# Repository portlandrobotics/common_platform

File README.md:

<!-- PROJECT SHIELDS -->
<!--
*** I'm using markdown "reference style" links for readability.
*** Reference links are enclosed in brackets [ ] instead of parentheses ( ).
*** See the bottom of this document for the declaration of the reference variables
*** for contributors-url, forks-url, etc. This is an optional, concise syntax you may use.
*** https://www.markdownguide.org/basic-syntax/#reference-style-links
-->
[![Contributors][contributors-shield]][contributors-url]
[![Forks][forks-shield]][forks-url]
[![Stargazers][stars-shield]][stars-url]
[![Issues][issues-shield]][issues-url]
[![MIT License][license-shield]][license-url]

<!-- PROJECT LOGO -->
<br />
<div align="center">

  <h3 align="center">Portland Area Robotics Society -- Common Robotics Platform</h3>

  <p align="center">
    Build and master the Common Robotics Platform with Portland Area Robotics Society 
    <br />
    <a href="https://parts-common-platform.readthedocs.io/en/latest/"><strong>Explore the docs »</strong></a>
    <br />
    <br />
    <a href="https://github.com/portlandrobotics/common_platform">View Demo</a>  <!-- TODO We need to add a demo video here -->
    ·
    <a href="https://github.com/portlandrobotics/common_platform/issues">Report Bug</a>
    ·
    <a href="https://github.com/portlandrobotics/common_platform/issues">Request Feature</a>
  </p>
</div>

<!-- TABLE OF CONTENTS -->
<details>
  <summary>Table of Contents</summary>
  <ol>
    <li>
      <a href="#about-the-project">About The Project</a>
      <ul>
        <li><a href="#built-with">Built With</a></li>
      </ul>
    </li>
    <li>
      <a href="#getting-started">Getting Started</a>
      <ul>
        <li><a href="#prerequisites">Prerequisites</a></li>
        <li><a href="#installation">Installation</a></li>
      </ul>
    </li>
    <li><a href="#usage">Usage</a></li>
    <li><a href="#roadmap">Roadmap</a></li>
    <li><a href="#contributing">Contributing</a></li>
    <li><a href="#license">License</a></li>
    <li><a href="#contact">Contact</a></li>
    <li><a href="#acknowledgments">Acknowledgments</a></li>
  </ol>
</details>

<!-- ABOUT THE PROJECT -->
## About The Project

<br>
<p align="center">
  
</p>
<br>

Our project centers around the innovative construction and programming of a versatile robot using the robust Pololu Romi Chassis Kit as its foundation. At the heart of our design is a custom carrier PCB, which integrates seamlessly with the chassis, ensuring a compact and efficient layout. 

<br>
<p align="center">
  
<br>
<br>

Key components of our build include two TB9051FTG Single Brushed DC Motor Driver Carriers for precise motion control, and a Pololu 5V, 2.5A Step-Down Voltage Regulator D24V22F5 to ensure stable power supply. Navigation and orientation are handled by the sophisticated MPU-9250 9DOF Module, a nine-axis sensor that offers unparalleled accuracy in movement tracking. Additional hardware includes a set of Romi Encoders, a Romi Chassis Caster for stable maneuverability, and a powerful Teensy 4.0 microcontroller for robust processing capabilities. We've also incorporated an SPDT slide switch and two IRFU5505PBF transistors, supported by a suite of nine resistors of varying values to fine-tune our circuitry. 

<br>
<p align="center">
  
</p>
<br>

Looking towards the future, our vision is to enhance this platform by integrating a Raspberry Pi, aiming to achieve autonomous functionality through the advanced capabilities of ROS2. This robot is not just a machine, but a gateway to exploring the vast possibilities of robotics, making it an ideal platform for enthusiasts and innovators alike in the Portland Area Robotics Society.

<p align="right">(<a href="#readme-top">back to top</a>)</p>

### Built With

* [![CPP][cpp]][cpp-url]
* [![C][c]][c-url]
* [![Python 3][python]][python-url]
* [![PlatformIO][platformio]][platformio-url]
* [![Arduino][arduino-ide]][arduino-url]
* [![KiCadEDA][kicad]][kicad-url]
* [![ROS][ros]][ros-url]

<p align="right">(<a href="#readme-top">back to top</a>)</p>

<!-- GETTING STARTED -->
## Getting Started

### Prerequisites

* All the required parts from the BOM on hand. [BOM](/BOM.csv)
* Windows/Mac/Linux PC
* Soldering supplies

### Installation

Welcome to the setup guide for the PARTS Common Robotics Platform. Follow these steps to prepare your hardware and software for an exciting journey into robotics!

#### 1. Solder Your PARTS CRP Board
Soldering the PARTS CRP board is the first crucial step. Follow the instructions carefully to ensure a successful setup.

- **Interactive BOM**: Utilize the [Interactive BOM](https://htmlpreview.github.io/?https://github.com/portlandrobotics/common_platform/blob/master/hardware/romi_board/bom/ibom.html) for an easier soldering process.
- **Headers for Connectivity**: We recommend using headers for connections between boards. This makes disassembly possible if needed.
  - Use female (socket) headers on the bottom board.
  - Use male (pin) headers on the top board. These are typically included with all breakout boards.
- **MOSFET Orientation**: Ensure the correct orientation of the MOSFETs during soldering.
- **Resistor for Battery Voltage Divider**: Choose the resistor based on your battery choice:
  - Use a 2M ohm resistor (R1) for 6 AA batteries.
  - Opt for a 3M ohm resistor if using higher voltage batteries like 2 LiPo batteries.
  - Install a >100 pf capacitor across R2 to address voltage drop issues.
- **Teensy Board Modification**: For battery power, cut the trace on the Teensy board. Refer to the note "Cut to separate VIN from VUSB" on the [Teensy 4.0 Back Side](https://github.com/portlandrobotics/common_platform/blob/master/hardware/main_schematic.pdf) image.
- **Resistor Values**: The values of R4, R5, R8, R9 depend on your specific usage. For I2C, 4.7k is appropriate.
- **Schematic**: Refer to the [Main Schematic](https://github.com/portlandrobotics/common_platform/blob/master/hardware/main_schematic.pdf) for detailed understanding.

#### 2. Solder Accessories
Solder accessories like the Inertial Measurement Unit (IMU), ensuring proper orientation and connection.

#### 3. Assemble the Pololu Romi Chassis
The Pololu Romi Chassis forms the physical structure of your robot.

- Follow the [Romi Chassis Assembly Guide](https://www.pololu.com/docs/0J68/4) for detailed instructions on assembling the chassis.

#### 4. Install Arduino IDE
The Arduino Integrated Development Environment (IDE) is essential for programming your robot.

- Download and install the [Arduino IDE](https://www.arduino.cc/en/Main/Software) suitable for your operating system.

#### 5. Clone PARTS CRP Repository
Get the latest codebase for the PARTS CRP project by cloning the repository.

- Use Git to clone the repository or download it directly from the [PARTS CRP GitHub page](https://github.com/portlandrobotics/common_platform).

_For detailed instructions, please refer to the [Documentation](https://parts-common-platform.readthedocs.io/en/latest/)_

<p align="right">(<a href="#readme-top">back to top</a>)</p>

## Usage

This section provides practical examples of how to use the PARTS Common Robotics Platform effectively. We'll start with a basic test to ensure your setup is functioning correctly.

### Starting with the Basic Test

1. **Flash the Teensy 4.0 Board:**
   Begin by flashing the Teensy 4.0 board with the basic test code found in the repository at `/firmware/basic_test/basic_test.ino`. This initial test is crucial for validating your setup.

2. **Expected Behavior:**
   Upon successful flashing, the robot should exhibit a simple behavior pattern: moving forward, pausing, and then moving backward.

_For more examples, please refer to the [Documentation](https://parts-common-platform.readthedocs.io/en/latest/)_

<p align="right">(<a href="#readme-top">back to top</a>)</p>

<!-- ROADMAP -->
## Roadmap

- [ ] Build hardware library for common robotics platform
- [ ] Build manual for open robotics platform
     - [ ] SBC
     - [ ] Microcontroller
     - [ ] Software
     - [ ] Power
     - [ ] Motion
     - [ ] Communication
     - [ ] Sensors and cameras
     - [ ] Soldering
     - [ ] PCB design and ordering
- [ ] Create 3D model of platform for Gazebo and other sims
- [ ] ROS2 Setup
    - [ ] micro-ROS + ROS2 Humble
    - [ ] control
    - [ ] commuication
    - [ ] navigation
    - [ ] avoidance
 - [ ] Demo of system

See the [open issues](https://github.com/portlandrobotics/common_platform/issues) for a full list of proposed features (and known issues).

<p align="right">(<a href="#readme-top">back to top</a>)</p>

<!-- CONTRIBUTING -->
## Contributing

Contributions are what make the open source community such an amazing place to learn, inspire, and create. Any contributions you make are **greatly appreciated**.

If you have a suggestion that would make this better, please fork the repo and create a pull request. You can also simply open an issue with the tag "enhancement".
Don't forget to give the project a star! Thanks again!

1. Fork the Project
2. Create your Feature Branch (`git checkout -b feature/AmazingFeature`)
3. Commit your Changes (`git commit -m 'Add some AmazingFeature'`)
4. Push to the Branch (`git push origin feature/AmazingFeature`)
5. Open a Pull Request

<p align="right">(<a href="#readme-top">back to top</a>)</p>

<!-- LICENSE -->
## License

Distributed under the MIT License and the Solderpad Hardware License v2.1. See [LICENSE.txt][license-url] for more information.

<p align="right">(<a href="#readme-top">back to top</a>)</p>

<!-- MARKDOWN LINKS & IMAGES -->
<!-- https://www.markdownguide.org/basic-syntax/#reference-style-links -->
[contributors-shield]: https://img.shields.io/github/contributors/portlandrobotics/common_platform.svg?style=for-the-badge
[contributors-url]: https://github.com/portlandrobotics/common_platform/graphs/contributors
[forks-shield]: https://img.shields.io/github/forks/portlandrobotics/common_platform.svg?style=for-the-badge
[forks-url]: https://github.com/portlandrobotics/common_platform/network/members
[stars-shield]: https://img.shields.io/github/stars/portlandrobotics/common_platform.svg?style=for-the-badge
[stars-url]: https://github.com/portlandrobotics/common_platform/stargazers
[issues-shield]: https://img.shields.io/github/issues/portlandrobotics/common_platform.svg?style=for-the-badge
[issues-url]: https://github.com/portlandrobotics/common_platform/issues
[license-shield]: https://img.shields.io/badge/license-mit_%26_solderpad-brightgreen?style=for-the-badge
[license-url]: https://github.com/portlandrobotics/common_platform/blob/master/LICENSE.txt
[arduino-ide]: https://img.shields.io/badge/Arduino_IDE-00979D?style=for-the-badge&logo=arduino&logoColor=white
[arduino-url]: https://www.arduino.cc/en/software
[cpp]: https://img.shields.io/badge/C%2B%2B-00599C?style=for-the-badge&logo=c%2B%2B&logoColor=white
[cpp-url]: https://en.wikipedia.org/wiki/C%2B%2B
[c]: https://img.shields.io/badge/C-00599C?style=for-the-badge&logo=c&logoColor=white
[c-url]: https://en.wikipedia.org/wiki/C_(programming_language)
[python]: https://img.shields.io/badge/Python-3776AB?style=for-the-badge&logo=python&logoColor=white
[python-url]: https://www.python.org/
[platformio]: https://img.shields.io/badge/PlatformIO-F5822A.svg?style=for-the-badge&logo=PlatformIO&logoColor=white
[platformio-url]: https://platformio.org/
[kicad]: https://img.shields.io/badge/KiCad-314CB0.svg?style=for-the-badge&logo=KiCad&logoColor=white
[kicad-url]: https://www.kicad.org/
[ros]: https://img.shields.io/badge/ROS-22314E.svg?style=for-the-badge&logo=ROS&logoColor=white
[ros-url]:https://www.ros.org/

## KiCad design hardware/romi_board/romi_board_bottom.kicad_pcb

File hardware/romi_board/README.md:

## Assembly Notes

- In general, follow the instructions in the Romi chassis assembly [guide](https://www.pololu.com/docs/0J68/4).  Note that wheel encoders should be installed as shown in those instructions and will plug into the bottom board.
- The [interactive BOM](https://htmlpreview.github.io/?https://github.com/portlandrobotics/common_platform/blob/master/hardware/romi_board/bom/ibom.html) is helpful while soldering components onto the board.
- We recommend using headers between the boards so that disassembly is possible.  Use female (socket) header on the bottom board and male (pin) headers on top board.  Pin headers come with all of the breakout boards.  
 
- Use the top board to guide breakout board header soldering.  Insert the pin headers into the appropriate positions on the top board and then add the breakout boards onto the pins and solder them to the breakout boards. 
We recommend using socket headers on the top board for all of the breakout board positions so that they can be plugged in- Brace the IMU with extra header or cardboard or some other means.  Shown below is a 3D printed block but anything of the appropriate size will do.  

- The three pin header on the motor driver is not needed and can be left without header pins.
- Pay attention to the orientation of the MOSFETs
- Use 2M ohm resistor for the battery voltage resistor divider (R1) if you use the 6 AA batteries.  If you use higher voltage batteries (2 LiPo batteries for example) then use a 3M ohm resistor.
- Cut trace on teensy for battery power.  See the note "Cut to separate VIN from VUSB" on the "Teensy 4.0 Back Side" image on this [page](https://www.pjrc.com/store/teensy40.html).
- If you want to mount a Raspberry Pi on the robot, this is how to use standoffs to do so:

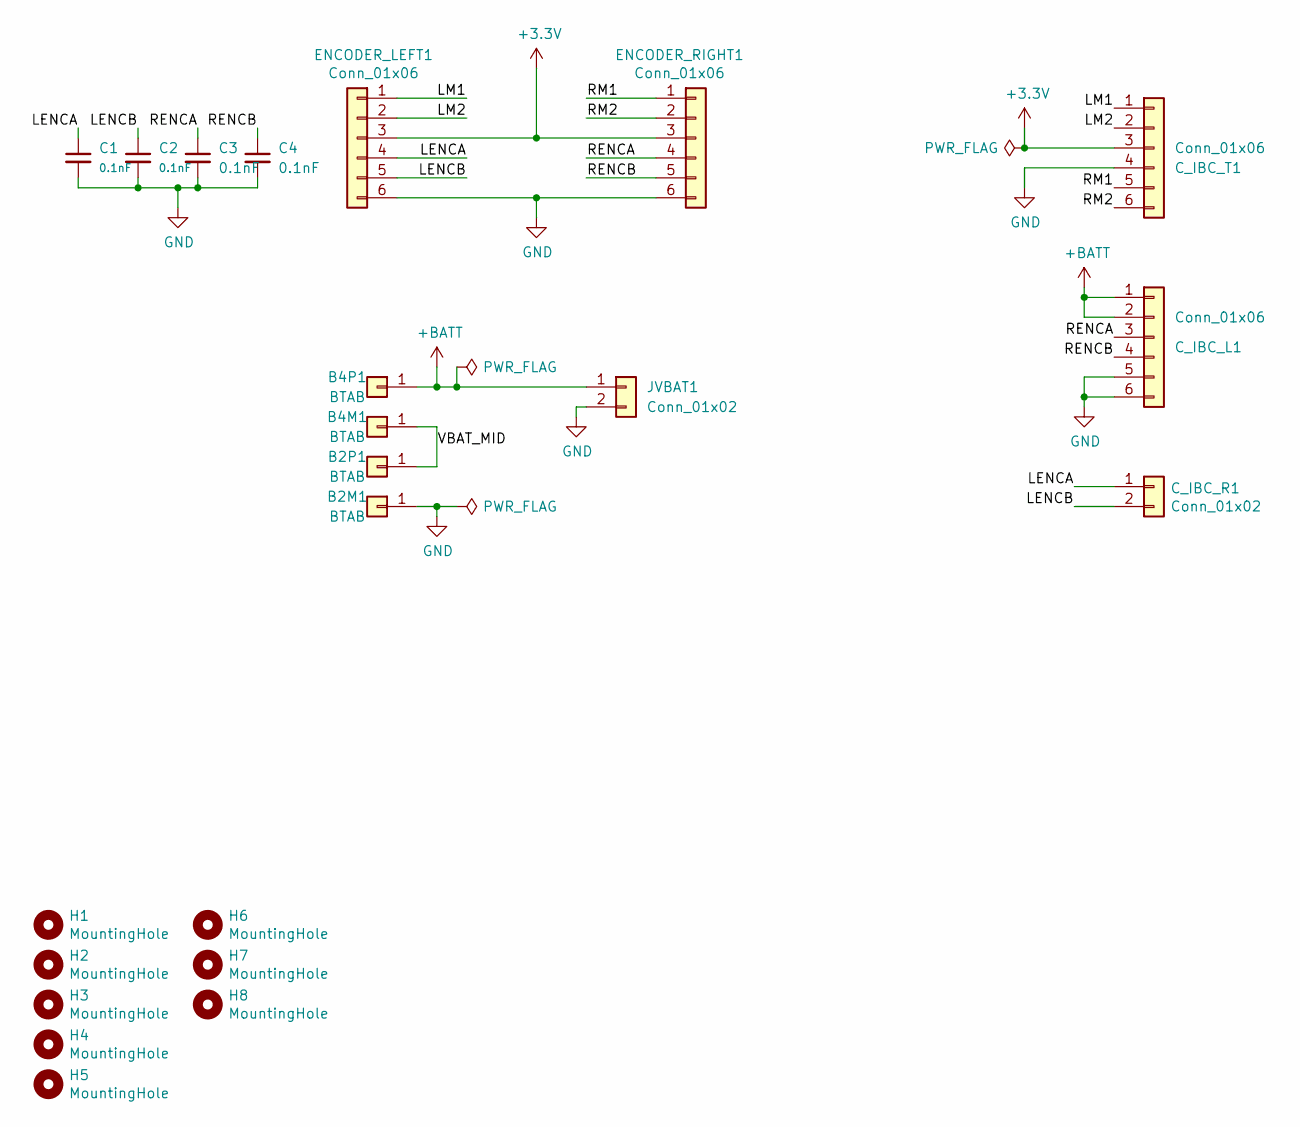
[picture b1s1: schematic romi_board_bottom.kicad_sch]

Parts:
B2M1, B2P1, B4M1, B4P1: BTAB; romi_battery_tab
C1, C2, C3, C4: 0.1nF; C_0805_2012Metric_Pad1.18x1.45mm_HandSolder
C_IBC_L1: Conn_01x06; PinHeader_1x06_P2.54mm_Vertical
C_IBC_R1: Conn_01x02; PinHeader_1x02_P2.54mm_Vertical
C_IBC_T1: Conn_01x06; PinHeader_1x06_P2.54mm_Vertical
ENCODER_LEFT1: Conn_01x06; PinHeader_1x06_P2.54mm_Vertical
ENCODER_RIGHT1: Conn_01x06; PinHeader_1x06_P2.54mm_Vertical
H1, H2, H3, H4, H5, H6: MountingHole; MountingHole_2.5mm
H7, H8: MountingHole; MountingHole_6mm
JVBAT1: Conn_01x02; PinHeader_1x02_P2.54mm_Vertical

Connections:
+3.3V: C_IBC_T1.3, ENCODER_LEFT1.3, ENCODER_RIGHT1.3
+BATT: B4P1.1, C_IBC_L1.1, C_IBC_L1.2, JVBAT1.1
/LENCA: C1.1, C_IBC_R1.1, ENCODER_LEFT1.4
/LENCB: C2.1, C_IBC_R1.2, ENCODER_LEFT1.5
/LM1: C_IBC_T1.1, ENCODER_LEFT1.1
/LM2: C_IBC_T1.2, ENCODER_LEFT1.2
/RENCA: C3.1, C_IBC_L1.3, ENCODER_RIGHT1.4
/RENCB: C4.1, C_IBC_L1.4, ENCODER_RIGHT1.5
/RM1: C_IBC_T1.5, ENCODER_RIGHT1.1
/RM2: C_IBC_T1.6, ENCODER_RIGHT1.2
/VBAT_MID: B2P1.1, B4M1.1
GND: B2M1.1, C1.2, C2.2, C3.2, C4.2, C_IBC_L1.5, C_IBC_L1.6, C_IBC_T1.4, ENCODER_LEFT1.6, ENCODER_RIGHT1.6, JVBAT1.2

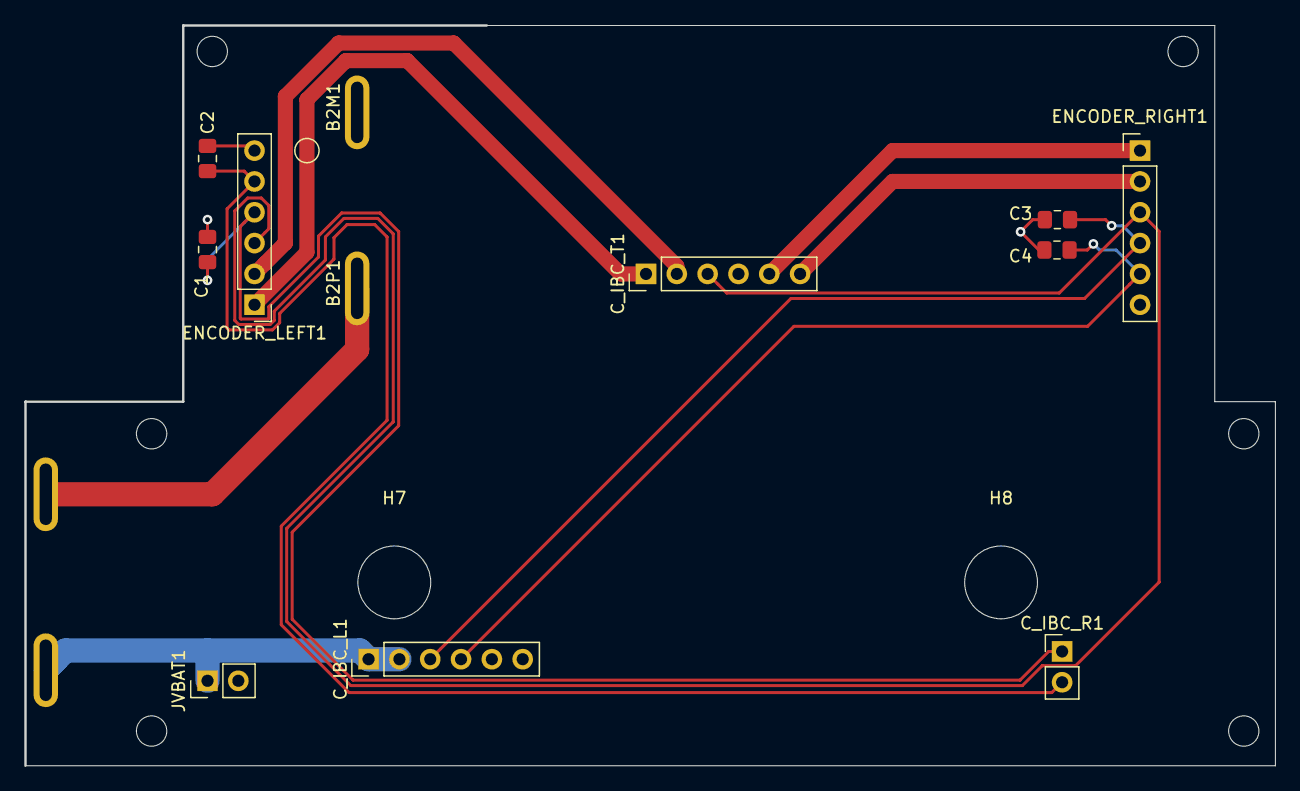
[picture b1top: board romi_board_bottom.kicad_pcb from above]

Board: 2 copper layers, 102.9 x 61.0 mm, 22 parts (0 on the bottom side), 12 nets.

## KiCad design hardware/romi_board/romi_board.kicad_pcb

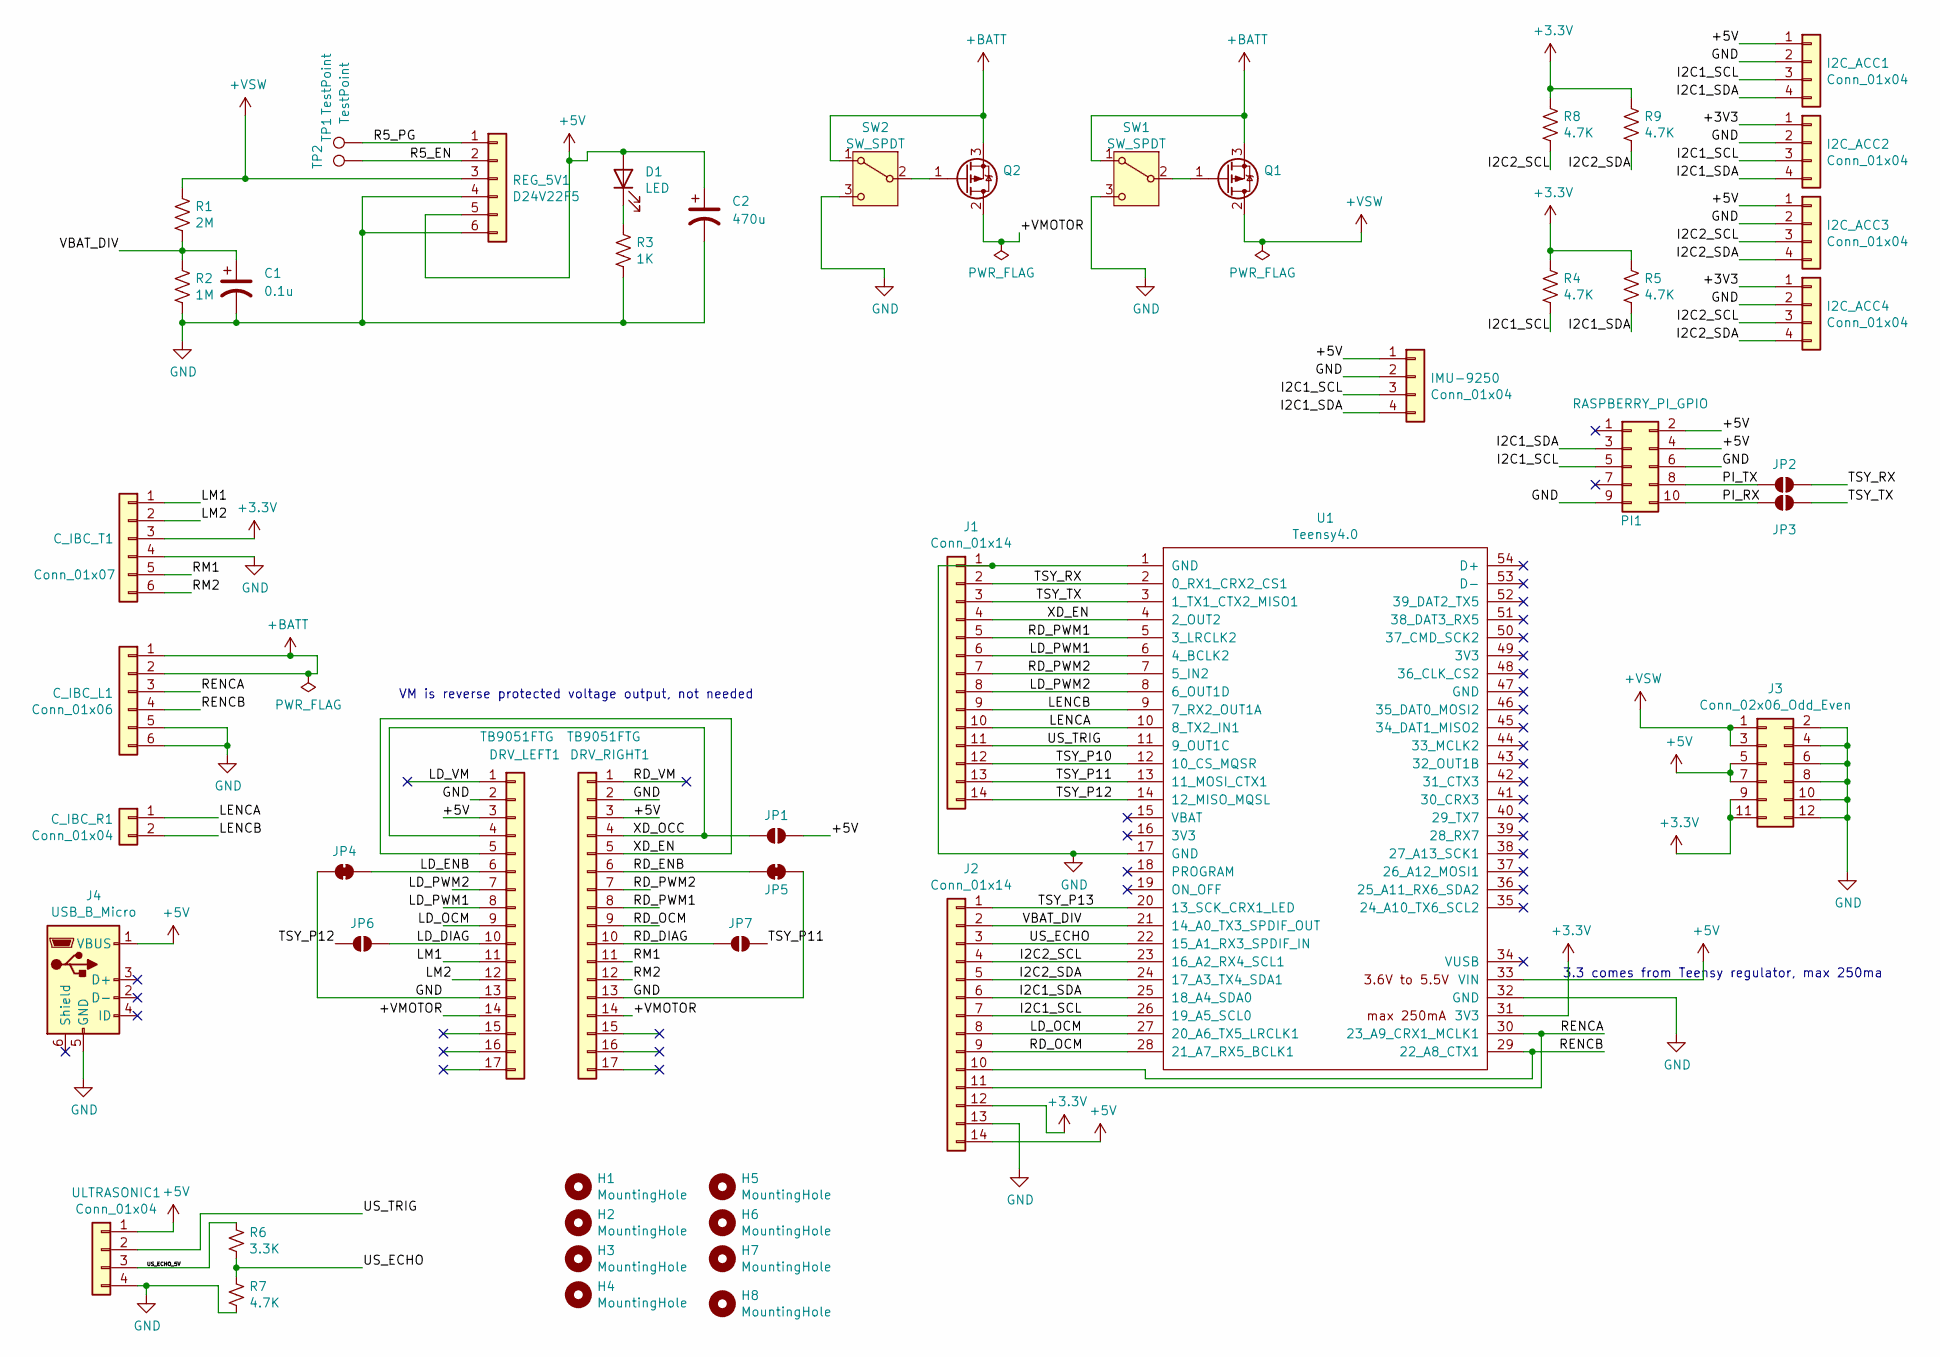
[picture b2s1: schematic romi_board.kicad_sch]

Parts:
C1: 0.1u; C_Disc_D5.0mm_W2.5mm_P5.00mm
C2: 470u; CP_Radial_D6.3mm_P2.50mm
C_IBC_L1: Conn_01x06; PinHeader_1x06_P2.54mm_Vertical
C_IBC_R1: Conn_01x04; PinHeader_1x02_P2.54mm_Vertical
C_IBC_T1: Conn_01x07; PinHeader_1x06_P2.54mm_Vertical
D1: LED; LED_D5.0mm
DRV_LEFT1: TB9051FTG; TB9051FTG_db
DRV_RIGHT1: TB9051FTG; TB9051FTG_db
H1, H2, H3, H4: MountingHole; MountingHole_2.5mm
H5, H6, H7, H8: MountingHole; MountingHole_6mm_passthrough
I2C_ACC1, I2C_ACC2, I2C_ACC3, I2C_ACC4: Conn_01x04; PinHeader_1x04_P2.54mm_Vertical
IMU-9250: Conn_01x04; MPU9250_BB
J1, J2: Conn_01x14; PinHeader_1x14_P2.54mm_Vertical
J3: Conn_02x06_Odd_Even; PinHeader_2x06_P2.54mm_Vertical
J4: USB_B_Micro; USB_Micro-B_Molex_47346-0001
JP1, JP2, JP3, JP6, JP7: SolderJumper_2_Open; SolderJumper-2_P1.3mm_Open_RoundedPad1.0x1.5mm
JP4, JP5: SolderJumper_2_Bridged; SolderJumper-2_P1.3mm_Bridged_RoundedPad1.0x1.5mm
PI1: RASPBERRY_PI_GPIO; PinHeader_2x05_P2.54mm_Vertical
Q1, Q2: Q_PMOS_DGS; TO-251-3_Vertical
R1: 2M; R_Axial_DIN0309_L9.0mm_D3.2mm_P2.54mm_Vertical
R2: 1M; R_Axial_DIN0309_L9.0mm_D3.2mm_P2.54mm_Vertical
R3: 1K; R_Axial_DIN0309_L9.0mm_D3.2mm_P2.54mm_Vertical
R4, R5, R7, R8, R9: 4.7K; R_Axial_DIN0309_L9.0mm_D3.2mm_P2.54mm_Vertical
R6: 3.3K; R_Axial_DIN0309_L9.0mm_D3.2mm_P2.54mm_Vertical
REG_5V1: D24V22F5; D24V2F5_bb
SW1, SW2: SW_SPDT; Switch
TP1, TP2: TestPoint; TestPoint_Pad_D2.0mm
U1: Teensy4.0; Teensy40_simple
ULTRASONIC1: Conn_01x04; PinHeader_1x04_P2.54mm_Vertical

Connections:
+5V: C2.1, D1.2 (A), DRV_LEFT1.3, DRV_RIGHT1.3, I2C_ACC1.1, I2C_ACC3.1, IMU-9250.1, J2.14, J3.5, J3.7, J4.1 (VBUS), JP1.1 (A), PI1.2, PI1.4, REG_5V1.5, U1.33 (VIN), ULTRASONIC1.1
+BATT: C_IBC_L1.1, C_IBC_L1.2, Q1.3 (S), Q2.3 (S), SW1.1 (A), SW2.1 (A)
+VSW: J3.1, J3.3, Q1.2 (D), R1.1, REG_5V1.3
/+VMOTOR: DRV_LEFT1.14, DRV_RIGHT1.14, Q2.2 (D)
/I2C1_SCL: I2C_ACC1.3, I2C_ACC2.3, IMU-9250.3, J2.7, PI1.5, R4.2, U1.26 (19_A5_SCL0)
/I2C1_SDA: I2C_ACC1.4, I2C_ACC2.4, IMU-9250.4, J2.6, PI1.3, R5.2, U1.25 (18_A4_SDA0)
/I2C2_SCL: I2C_ACC3.3, I2C_ACC4.3, J2.4, R8.2, U1.23 (16_A2_RX4_SCL1)
/I2C2_SDA: I2C_ACC3.4, I2C_ACC4.4, J2.5, R9.2, U1.24 (17_A3_TX4_SDA1)
/LD_DIAG: DRV_LEFT1.10, JP6.1 (A)
/LD_ENB: DRV_LEFT1.6, JP4.2 (B)
/LD_OCM: DRV_LEFT1.9, J2.8, U1.27 (20_A6_TX5_LRCLK1)
/LD_PWM1: DRV_LEFT1.8, J1.6, U1.6 (4_BCLK2)
/LD_PWM2: DRV_LEFT1.7, J1.8, U1.8 (6_OUT1D)
/LD_VM: DRV_LEFT1.1
/LENCA: C_IBC_R1.1, J1.10, U1.10 (8_TX2_IN1)
/LENCB: C_IBC_R1.2, J1.9, U1.9 (7_RX2_OUT1A)
/LM1: C_IBC_T1.1, DRV_LEFT1.11
/LM2: C_IBC_T1.2, DRV_LEFT1.12
/PI_RX: JP3.1 (A), PI1.10
/PI_TX: JP2.1 (A), PI1.8
/R5_EN: REG_5V1.2, TP2.1
/R5_PG: REG_5V1.1, TP1.1
/RD_DIAG: DRV_RIGHT1.10, JP7.2 (B)
/RD_ENB: DRV_RIGHT1.6, JP5.2 (B)
/RD_OCM: DRV_RIGHT1.9, J2.9, U1.28 (21_A7_RX5_BCLK1)
/RD_PWM1: DRV_RIGHT1.8, J1.5, U1.5 (3_LRCLK2)
/RD_PWM2: DRV_RIGHT1.7, J1.7, U1.7 (5_IN2)
/RD_VM: DRV_RIGHT1.1
/RENCA: C_IBC_L1.3, J2.11, U1.30 (23_A9_CRX1_MCLK1)
/RENCB: C_IBC_L1.4, J2.10, U1.29 (22_A8_CTX1)
/RM1: C_IBC_T1.5, DRV_RIGHT1.11
/RM2: C_IBC_T1.6, DRV_RIGHT1.12
/TSY_P10: J1.12, U1.12 (10_CS_MQSR)
/TSY_P11: J1.13, JP7.1 (A), U1.13 (11_MOSI_CTX1)
/TSY_P12: J1.14, JP6.2 (B), U1.14 (12_MISO_MQSL)
/TSY_P13: J2.1, U1.20 (13_SCK_CRX1_LED)
/TSY_RX: J1.2, JP2.2 (B), U1.2 (0_RX1_CRX2_CS1)
/TSY_TX: J1.3, JP3.2 (B), U1.3 (1_TX1_CTX2_MISO1)
/US_ECHO: J2.3, R6.2, R7.1, U1.22 (15_A1_RX3_SPDIF_IN)
/US_ECHO_5V: R6.1, ULTRASONIC1.3
/US_TRIG: J1.11, U1.11 (9_OUT1C), ULTRASONIC1.2
/VBAT_DIV: C1.1, J2.2, R1.2, R2.1, U1.21 (14_A0_TX3_SPDIF_OUT)
/XD_EN: DRV_LEFT1.5, DRV_RIGHT1.5, J1.4, U1.4 (2_OUT2)
/XD_OCC: DRV_LEFT1.4, DRV_RIGHT1.4, JP1.2 (B)
GND: C1.2, C2.2, C_IBC_L1.5, C_IBC_L1.6, C_IBC_T1.4, DRV_LEFT1.2, DRV_LEFT1.13, DRV_RIGHT1.2, DRV_RIGHT1.13, I2C_ACC1.2, I2C_ACC2.2, I2C_ACC3.2, I2C_ACC4.2, IMU-9250.2, J1.1, J2.13, J3.2, J3.4, J3.6, J3.8, J3.10, J3.12, J4.5 (GND), JP4.1 (A), JP5.1 (A), PI1.6, PI1.9, R2.2, R3.2, R7.2, REG_5V1.4, REG_5V1.6, SW1.3 (C), SW2.3 (C), U1.1 (GND), U1.17 (GND), U1.32 (GND), ULTRASONIC1.4
unnamed: D1.1 (K), R3.1
unnamed: Q1.1 (G), SW1.2 (B)
unnamed: Q2.1 (G), SW2.2 (B)

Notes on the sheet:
3.3 comes from Teensy regulator, max 250ma
VM is reverse protected voltage output, not needed

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
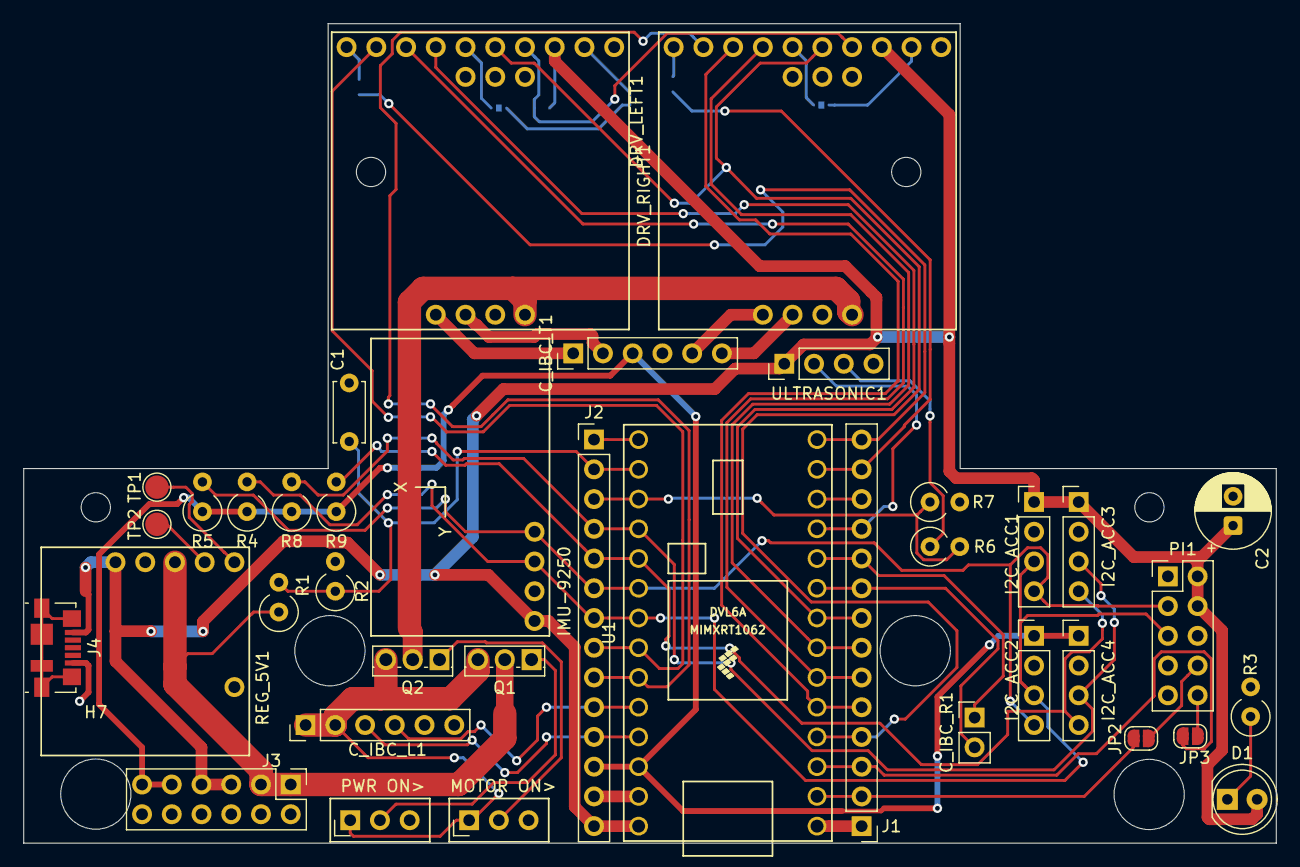
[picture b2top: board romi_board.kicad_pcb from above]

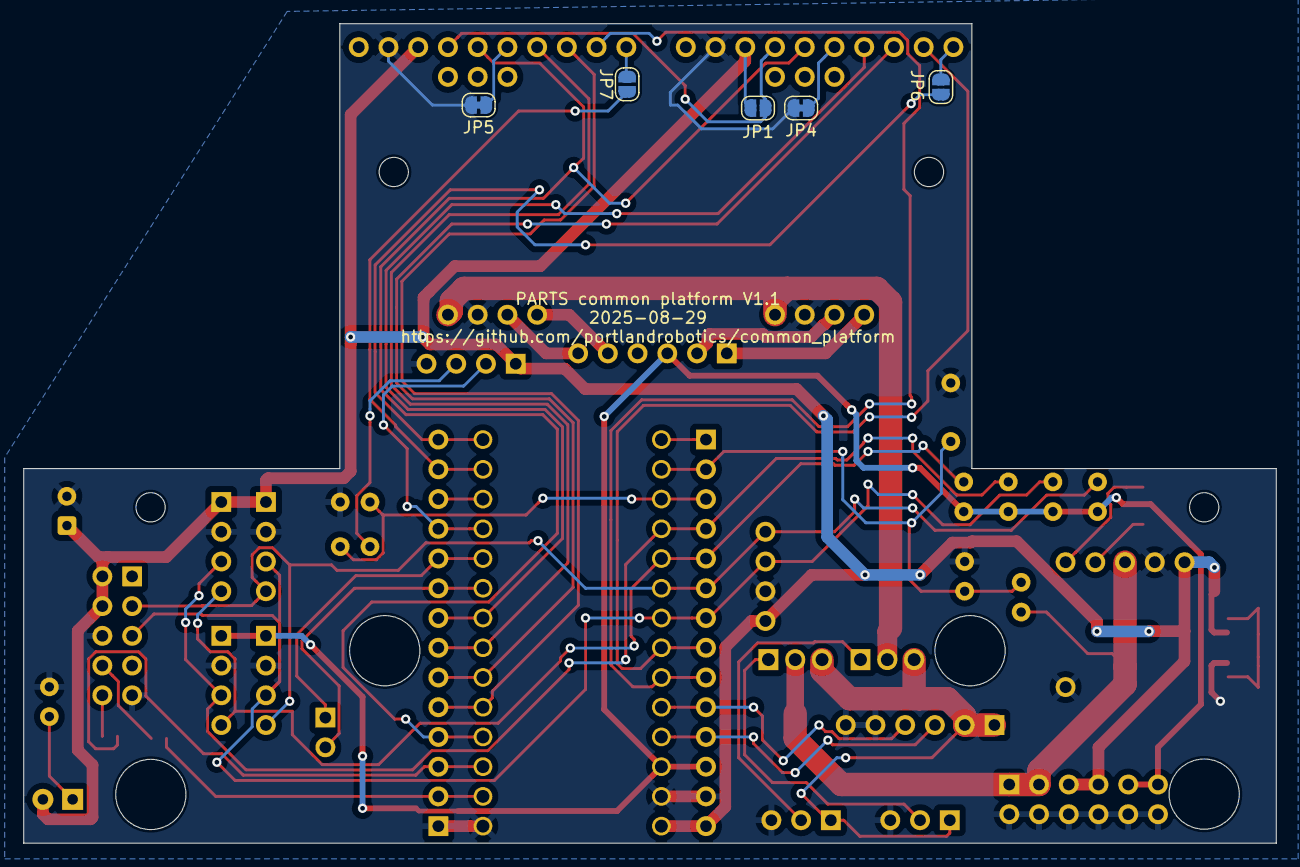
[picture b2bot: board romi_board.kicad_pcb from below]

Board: 2 copper layers, 107.0 x 70.0 mm, 51 parts (5 on the bottom side), 47 nets.

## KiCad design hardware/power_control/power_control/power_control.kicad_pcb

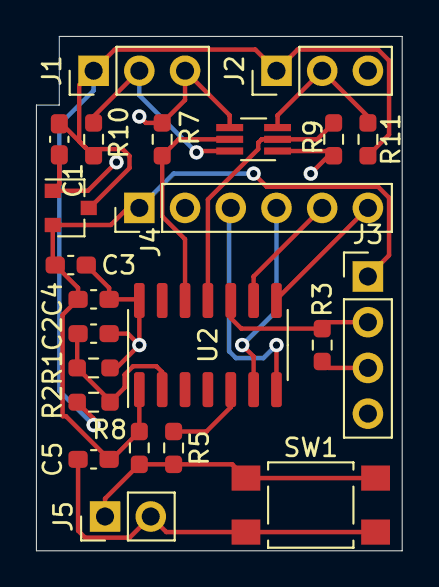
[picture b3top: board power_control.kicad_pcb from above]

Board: 2 copper layers, 20.3 x 28.6 mm, 23 parts (0 on the bottom side), 16 nets.

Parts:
C1, C2, C3, C4, C5: C; C_0603_1608Metric_Pad1.08x0.95mm_HandSolder
J1, J2: Conn_01x03; PinHeader_1x03_P2.54mm_Vertical
J3: Conn_01x04; PinHeader_1x04_P2.54mm_Vertical
J4: Conn_01x06; PinHeader_1x06_P2.54mm_Vertical
J5: Conn_01x02; PinHeader_1x02_P2.54mm_Vertical
J6: Conn_01x06; SOT-363_SC-70-6_Handsoldering
R1, R2, R3, R5, R7, R8, R9, R10, R11: R_Small_US; R_0603_1608Metric_Pad0.98x0.95mm_HandSolder
SW1: SW_Push; SW_SPST_TL3305A
U1: MCP1703A-5002_SOT23; SOT-23
U2: ATtiny1604-SS; SOIC-14_3.9x8.7mm_P1.27mm

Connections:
+3V3: C3.1, C4.1, C5.1, J3.1, J4.1, R8.2, U1.2, U2.1
+BATT: C1.1, J1.1, J2.1, R2.1, R10.1, R11.1, U1.3
/PSM: J2.2, J6.3, R11.2
/PSS: J1.2, J6.6, R10.2
/RX: J4.4, U2.6
/SCL: J4.5, U2.9
/SDA: J4.6, U2.8
/TX: J4.3, U2.7
/UPDI: J3.2, R3.2, U2.10
GND: C1.2, C2.2, C3.2, C4.2, C5.2, J1.3, J2.3, J3.4, J4.2, J5.2, J6.1, J6.4, R1.2, R7.2, R9.2, SW1.2, U1.1, U2.14
unnamed: C2.1, R1.1, R2.2, U2.2
unnamed: J3.3, R3.1
unnamed: J5.1, R5.2, R8.1, SW1.1
unnamed: J6.2, R9.1, U2.11
unnamed: J6.5, R7.1, U2.12
unnamed: R5.1, U2.5

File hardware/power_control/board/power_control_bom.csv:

Reference, Quantity, Value, Footprint,Digikey Part,MFG Part,Description, Datasheet
C1 C3 C4 ,3,2.2u,Capacitor_SMD:C_0603_1608Metric_Pad1.08x0.95mm_HandSolder,,,,~
C2 C5 ,2,100n,Capacitor_SMD:C_0603_1608Metric_Pad1.08x0.95mm_HandSolder,,,,~
J1 J2 ,2,Conn_01x03,Connector_PinHeader_2.54mm:PinHeader_1x03_P2.54mm_Vertical,,,,~
J3 ,1,Conn_01x04,Connector_PinHeader_2.54mm:PinHeader_1x04_P2.54mm_Vertical,,,,~
J4 ,1,Conn_01x06,Connector_PinHeader_2.54mm:PinHeader_1x06_P2.54mm_Vertical,,,,~
J5 ,1,Conn_01x02,Connector_PinHeader_2.54mm:PinHeader_1x02_P2.54mm_Vertical,,,,~
J6 ,1,,Package_TO_SOT_SMD:SOT-363_SC-70-6_Handsoldering,1727-2733-1-ND,NX138BKSX,MOSFET 2 N-CH 60V 210MA 6TSSOP,~
R1 ,1,330k,Resistor_SMD:R_0603_1608Metric_Pad0.98x0.95mm_HandSolder,,,,~
R2 ,1,1M,Resistor_SMD:R_0603_1608Metric_Pad0.98x0.95mm_HandSolder,,,,~
R3 ,1,4.7k,Resistor_SMD:R_0603_1608Metric_Pad0.98x0.95mm_HandSolder,,,,~
R5 ,1,1k,Resistor_SMD:R_0603_1608Metric_Pad0.98x0.95mm_HandSolder,,,,~
R7 R8 R9 R10 R11 ,5,10k,Resistor_SMD:R_0603_1608Metric_Pad0.98x0.95mm_HandSolder,,,,~
SW1 ,1,SW_Push,Button_Switch_SMD:SW_SPST_TL3305A,EG5350CT-ND,TL3305AF160QG,SWITCH TACTILE SPST-NO 50MA 12V,~
U1 ,1,MCP1703A-5002_SOT23,Package_TO_SOT_SMD:SOT-23,MCP1792T-3302H/CBCT-ND,MCP1792T-3302H/CB,IC REG LIN 3.3V 100MA SOT23A-3,http://ww1.microchip.com/downloads/en/DeviceDoc/20005122B.pdf
U2 ,1,ATtiny1604-SS,Package_SO:SOIC-14_3.9x8.7mm_P1.27mm,ATTINY1604-SSNRCT-ND,ATTINY1604-SSNR,IC MCU 8BIT 16KB FLASH 14SOIC,http://ww1.microchip.com/downloads/en/DeviceDoc/ATtiny804_16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

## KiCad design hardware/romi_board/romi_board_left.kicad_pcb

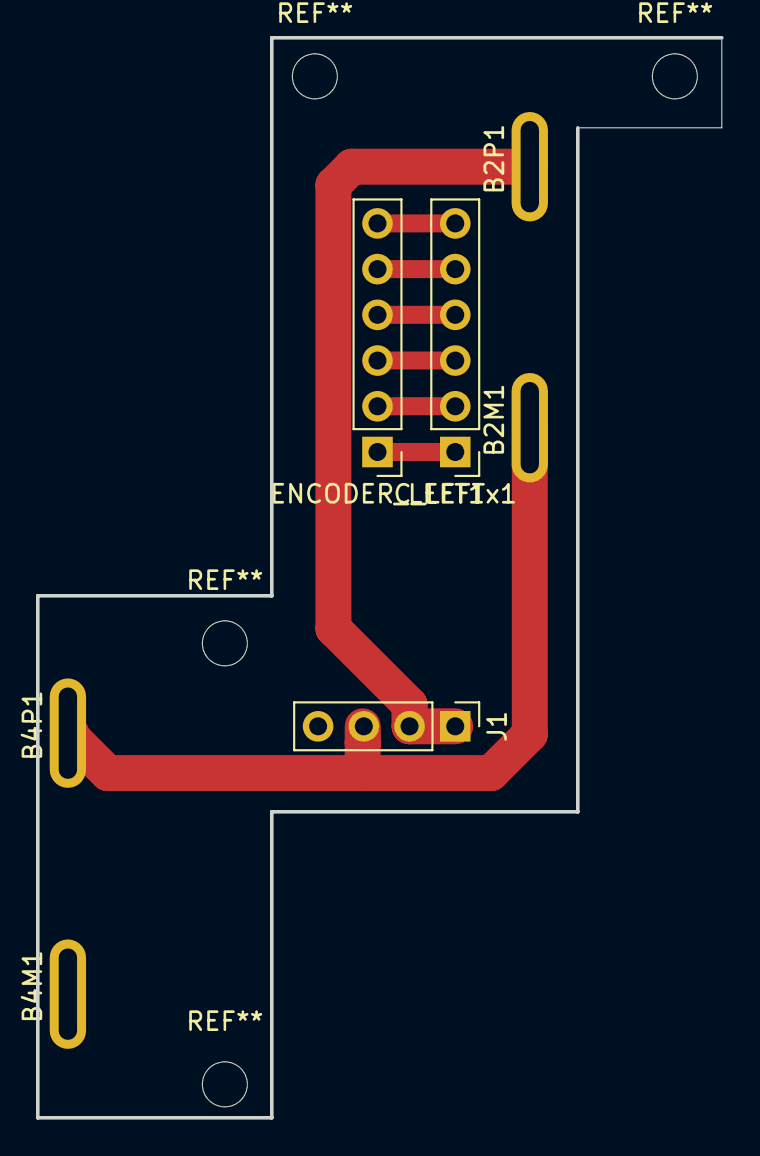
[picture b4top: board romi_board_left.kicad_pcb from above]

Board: 2 copper layers, 38.0 x 60.0 mm, 7 parts (0 on the bottom side), 8 nets.

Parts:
B2M1, B2P1, B4M1, B4P1: BTAB; romi_battery_tab
C_LEFTx1: Conn_01x07; PinHeader_1x06_P2.54mm_Vertical
ENCODER_LEFT1: Conn_01x06; PinHeader_1x06_P2.54mm_Vertical
J1: Conn_01x04; PinHeader_1x04_P2.54mm_Vertical

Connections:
+BATT: B2P1.1, J1.1, J1.2
/L5V: C_LEFTx1.3, ENCODER_LEFT1.3
/LENCAx: C_LEFTx1.4, ENCODER_LEFT1.4
/LENCBx: C_LEFTx1.5, ENCODER_LEFT1.5
/LM1x: C_LEFTx1.1, ENCODER_LEFT1.1
/LM2x: C_LEFTx1.2, ENCODER_LEFT1.2
/VBAT_MID: B2M1.1, B4P1.1, J1.3
GND: B4M1.1, C_LEFTx1.6, ENCODER_LEFT1.6, J1.4

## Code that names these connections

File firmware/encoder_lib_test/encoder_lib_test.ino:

//***********************************
// PARTS Common Robot Platform
// Test Program
//***********************************

#define PRINT_ENCODER_SPEED 1
#define ENCODER_USE_INTERRUPTS

#include <Encoder.h>

const int PIN_XD_EN   =  2;
const int PIN_RD_PWM1 =  3;
const int PIN_LD_PWM1 =  4;
const int PIN_RD_PWM2 =  5;
const int PIN_LD_PWM2 =  6;
const int PIN_LENCB   =  7;
const int PIN_LENCA   =  8;
const int PIN_US_TRIG =  9;
const int PIN_VBAT    = 14;
const int PIN_US_ECHO = 15;
const int PIN_LD_OCM  = 20;
const int PIN_RD_OCM  = 21;
const int PIN_RENCB   = 22;
const int PIN_RENCA   = 23;

#define RENC 0
#define LENC 1

long encCount[2] = {0, 0};
float lastEncSpeed[2] = {0, 0};
const char *wheelName[2] = {"Right", "Left"};

Encoder left(PIN_LENCB, PIN_LENCA);
Encoder right(PIN_RENCA, PIN_RENCB);

void setup()
{
	// Enable motor drive outputs
	pinMode(PIN_XD_EN, OUTPUT);
	pinMode(PIN_RD_PWM1, OUTPUT);
	pinMode(PIN_LD_PWM1, OUTPUT);
	pinMode(PIN_RD_PWM2, OUTPUT);
	pinMode(PIN_LD_PWM2, OUTPUT);

	// Make sure motors are off to start
	digitalWrite(PIN_XD_EN, HIGH);
	analogWrite(PIN_RD_PWM1, 0);
	analogWrite(PIN_RD_PWM2, 0);
	analogWrite(PIN_LD_PWM1, 0);
	analogWrite(PIN_LD_PWM2, 0);
}

// use PJRC Encoder library

void loop()
{
	static int32_t lastEnc[2] = {0, 0};
	static unsigned long lastEncTime[2] = {0, 0};
	static int dir[2] = {1, 1};
	static bool first = true;
	unsigned long nowMicros = micros();
	const unsigned long nowMillis = millis();
	static long dt[2] = {0, 0};
	int32_t enc[2] = {0, 0};
	float speed[2];
	int i;

	enc[RENC] = right.read();
  enc[LENC] = left.read();

	if (first) {
		first = false;
		lastEnc[0] = enc[0];
		lastEnc[1] = enc[1];
	}

	for (i = 0; i < 2; i++) {
		if (enc[i] != lastEnc[i]) {
			// 1440 counts per revolution
			// 70mm diameter
			// 1 revolution = Pi * 70mm = 220 mm / rev
			// 1 count = Pi * 70mm / 1440 = 153 um / count

			dt[i] = nowMicros - lastEncTime[i];
			lastEncTime[i] = nowMicros;

			dir[i] = (enc[i] >= lastEnc[i]) ? 1 : -1;
			lastEnc[i] = enc[i];

			encCount[i] = enc[i];

			speed[i] = 153. / dt[i]; // micrometers / microsecond => m/s
			lastEncSpeed[i] = speed[i] * dir[i];
		}
	}

	// print distance and speed
	for (i = 0; i < 2; i++) {
		static unsigned long nextPrintRead[2] = {0, 0};

		if (nowMillis > nextPrintRead[i]) {
			Serial.print(wheelName[i]);
			Serial.print(" ");
			Serial.print(dt[i] / 1e3);
			Serial.print(" msec, dir ");
			Serial.print(dir[i]);
			Serial.print(" total ");
			Serial.print(encCount[i] * 153e-6);
			Serial.print(" meters, speed ");
			Serial.print(lastEncSpeed[i]);
			Serial.println(" m/s");
			nextPrintRead[i] = nowMillis + 1000;
		}
	}
}

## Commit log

2020-04-29 Roll back to KiCAD v5.1.2 and add project specific libraries
2020-05-02 Add BOM
2020-05-02 fix directory structure
2020-05-02 Add teensy symbol library
2020-05-03 Make library paths relative.
2020-05-03 Add footprints for breakout boards
2020-05-03 Initial version of schematics and boards.
2020-05-04 Create simplified footprint for teensy
2020-05-04 flip the left motor encorder connector the right way round.
2020-06-09 Redesign to use two boards instead of 3
2020-06-26 Added switches, optional USB power connector, changed out mouting holes, a few reroutes for SI
2020-06-28 Update BOM
2020-07-11 Cosmetic schematic changes and added PDF's of the boards and schematics.
2020-08-01 Add resistor values to schematic
2020-08-01 Add interactive BOM
2020-09-15 Add initial test firmware
2020-09-28 Add assembly notes in readme for romi hardware desing
2020-09-29 add Raspberry Pi mounting instructions
2020-11-10 Fix power/ground terminal swap.
2020-11-10 simple closed loop motor control test code
2021-01-12 add encoder-only test add PJRC Encoder library test improve basic_test - use both wheels - improve integrator in PID - add conditionals to turn on/off features - improve motor ramp to ramp both forwa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
2021-08-24 substantial rewrite of closed loop motor test code
2021-09-05 cosmetic changes: net names and component values
2021-09-05 Initial revision, as fabbed 20210823
2021-09-05 folder rename
2021-09-05 add firmware and software for power_control board
2021-09-05 Initial port to micro-ros, using cmd_vel topic and Twist messages
2022-11-07 Add code for reconnection to micro-ros-agent
2022-12-01 Add modified platform.txt file for teensy micro_ros library
2022-12-16 Fixed motor control loop for twist messages
2022-12-16 clean up
2022-12-16 remove unused variables and cleanup
2022-12-27 Fix angular velocity calculation
2023-01-07 Added schematic PDF and BOM.
2023-02-07 Fix PID constants to be equal (left and right). Improve uros agent connectivity
2023-11-29 Started with new README.md
2023-11-29 readme update
2023-11-29 update to readme
2023-11-29 updated license
2023-11-30 added sphinx files
2023-11-30 updated to sphinx theme
2023-11-30 updated extensions
2023-11-30 extension add
2023-11-30 Updated docs
2023-11-30 change conf
2023-11-30 sphinx install
2023-11-30 sphinx run
2023-11-30 added python packages
2023-11-30 sphinx change
2023-11-30 added requirements file
2023-11-30 yaml update
2023-11-30 changed python packages.
2023-11-30 fixed copyright
2023-11-30 changed docs to link to new readthedocs repository
2023-11-30 adding blank docs
2023-11-30 fix contents
2023-11-30 update indexx
2023-11-30 index
2023-11-30 test
2023-11-30 changed main pics
2023-11-30 Updated photos
2023-11-30 readme changes
2023-11-30 Updated docs to include templates
2023-11-30 change toctree
2023-11-30 static change
2023-11-30 docs edit
2023-11-30 Updated name
2023-11-30 Title changes
2023-11-30 added _todos
2023-11-30 added 3d print for imu
2023-11-30 changed docs title
2023-11-30 added 3d printing doc template
2023-11-30 fixed logo
2023-12-02 update sbus test
2023-12-03 removed all unneeded code for sbus test
2023-12-04 Update readme and sbus_test
2023-12-04 adding serial logging and comments
2023-12-04 Formatted
2023-12-04 more readme. updates
2023-12-04 readme addition
2023-12-04 Edit
2023-12-04 Added proper comments
2023-12-04 Updated comments on basic test
2023-12-04 Added failsafe for SBUS- resturctured loop
2023-12-05 Fixed logging and failsafe on sbus
2023-12-11 logo fix
2023-12-16 ultrasonic sensor first commit
2023-12-16 folder changes
2023-12-18 Update README.md
    Fixed License badge
2023-12-18 fixed license badge
2023-12-18 Fixed License Shield
2024-01-20 gitignore
2024-01-20 Remove .vscode from tracking
2024-01-20 roadmap changes
2025-02-25 Combine master branch code for closed_loop.ino with uROS changes from this branch, using conditional compilation flag to choose which version to use. WIP (compiles but not yet tested on hardware)
2025-02-25 Corrected last checkin code
2025-02-26 Fix compile for non ROS case
2025-04-19 Clean up formatting of code
2025-04-25 Improve PID class (WIP)
2025-05-03 1. Change application of PID factor to directly control motor speed instead of integrating it 2. Improve code organization with respect to ROS/Standalone conditional compilation 3. Improve variable e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
2025-05-13 Change motor encoder handling to use interupts to count pulses. Tune up PID parameters to actually achieve target speed. Additional code cleanups.
2025-05-22 add some more comments
2025-06-07 Add comments
2025-06-08 Clean up unecessary variables
2025-06-28 Split code into multiple files
2025-07-28 Update to micro-ros version Humble. No code changes necessary.
2025-08-29 Add power header and filter capacitors to bottom. Add filter capacitors to top.
2025-09-07 Minor cleanup of comments
